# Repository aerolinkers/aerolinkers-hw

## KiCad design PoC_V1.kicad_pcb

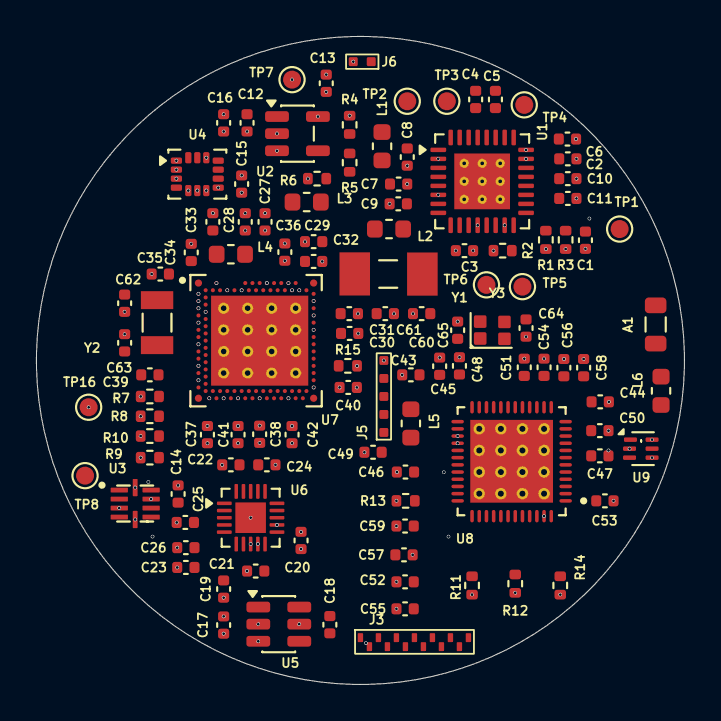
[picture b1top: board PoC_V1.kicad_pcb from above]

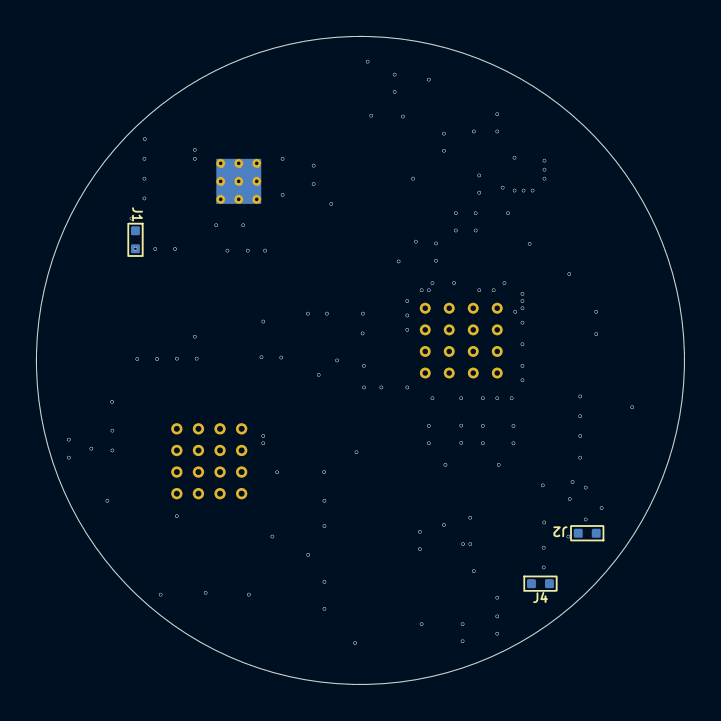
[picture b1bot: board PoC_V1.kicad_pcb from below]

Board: 4 copper layers, 36.0 x 36.0 mm, 114 parts (3 on the bottom side), 88 nets, no tracks yet.

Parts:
A1: ACA-5036-A2-CC-S - 2.4 GHz; L_0805_2012Metric
C1, C2, C4, C5, C6, C12, C14, C22, C26, C27, C28, C29, C32, C33, C45, C48, C57: 1uF; C_0402_1005Metric
C3, C15, C16, C20, C21, C23, C24, C25, C30, C34, C35, C36, C37, C38, C39, C40, C41, C42, C50, C53: 100nF; C_0402_1005Metric
C7, C8, C9, C10, C11, C13: 10uF; C_0402_1005Metric
C17, C19, C43, C47, C49, C58: 4.7uF; C_0402_1005Metric
C18, C54: 0.22uF; C_0402_1005Metric
C31: 2.2nF; C_0402_1005Metric
C44, C59: 0.47uF; C_0402_1005Metric
C46: 10nF; C_0402_1005Metric
C51, C52, C55: 2.2uF; C_0402_1005Metric
C56, C60, C61, C62, C63, C64, C65: 22nF; C_0402_1005Metric
J1, J2, J4, J6: Conn_01x02; 2P_P1mm
J3: Conn_01x13; 13P_P1mm
J5: Conn_01x05; 5P_P1mm
L1, L2: 2.2uH; L_0603_1608Metric
L3, L4: 10uH; L_0603_1608Metric
L5: 3.3uH; L_0603_1608Metric
L6: 1.5nH; L_0603_1608Metric
R1: 270K; R_0402_1005Metric
R2, R11, R12, R13, R14: 100K; R_0402_1005Metric
R3, R15: 10K; R_0402_1005Metric
R4: 200K; R_0402_1005Metric
R5: 3K; R_0402_1005Metric
R6: 66.5K; R_0402_1005Metric
R7, R8, R9, R10: 3.3K; R_0402_1005Metric
TP1, TP2, TP3, TP4, TP5, TP6, TP7, TP8, TP16: TestPoint; TestPoint_Pad_D1.0mm
U1: NPM1300-QEAA-R7; QFN-32-1EP_5x5mm_P0.5mm_EP3.1x3.1mm_ThermalVias
U2: TPS76201; SOT-23-5
U3: DRV2603; WQFN-10
U4: LSM6DSOX; LGA-14_3x2.5mm_P0.5mm_LayoutBorder3x4y
U5: REG710NA-3.3/250; SOT-23-6
U6: SGTL5000; WQFN-20-1EP_3x3mm_P0.4mm_EP1.7x1.7mm
U7: NRF5340-QKAA-AB0-R; XCVR_NRF5340-QKAA-AB0-R
U8: NRF7002-QFAA-R; IC_NRF7002-QFAA-R
U9: DPX1608LKF3R2460A; 1608 Diplexer
Y1: 32MHz; YSX530GA
Y2: 32.768 KHz; XTAL_FC-135_32.7680KA-A0
Y3: 40 MHz; 40MHZ crystal_

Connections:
DISP_3.3V: C19.1, J3.1, U5.1 (VOUT)
DIS_BL: J3.9, U7.R31 (P1.10)
DIS_CS: J3.6, U7.AK24 (P1.07)
DIS_DC: J3.7, U7.AL23 (P1.08)
DIS_MISO: J3.3, U7.AL19 (P1.04)
DIS_MOSI: J3.4, U7.AK22 (P1.05)
DIS_RST: J3.8, U7.AK26 (P1.09)
DIS_SCLK: J3.5, U7.AL21 (P1.06)
DIS_TP_INT: J3.12, U7.B14 (P1.15)
DIS_TP_RST: J3.13, U7.B20 (P1.11)
GNDREF: C1.2, C2.2, C3.2, C4.2, C5.2, C6.2, C7.2, C8.2, C9.2, C10.2, C11.2, C12.2, C13.2, C14.2, C15.2, C16.2, C17.2, C19.2, C20.2, C21.2, C22.2, C23.2, C24.2, C25.2, C26.2, C27.2, C28.2, C29.2, C30.2, C31.2, C32.2, C33.2, C34.2, C35.2, C36.2, C37.2, C38.2, C39.2, C40.2, C41.2, C42.2, C43.2, C44.2, C45.2, C46.2, C47.2, C48.2, C49.2, C50.2, C51.2, C52.2, C53.2, C54.2, C55.2, C56.2, C57.2, C58.2, C59.2, C60.2, C61.1, C62.2, C63.1, C64.2, C65.1, J1.2, J3.2, J4.2, J5.5, J6.2, R1.2, R2.2, R3.1, R6.1, R11.1, R12.1, R13.2, R14.1, U1.2 (PVSS1), U1.6 (PVSS2), U1.15 (SHPHLD), U1.23 (CC1), U1.24 (CC2), U1.33 (PAD), U2.2 (GND), U2.3 (EN), U3.3 (LRA_/ERM), U3.5 (Gnd), U3.8 (Gnd), U3.10 (Gnd), U4.1 (SDO/SA0), U4.2 (SDx), U4.3 (SCx), U4.6 (GND), U4.7 (GND), U5.2 (GND), U6.8 (LINEIN_R), U6.9 (LINEIN_L), U6.21 (Gnd_PAD), U7.35 (VSS_PAD), U7.36 (VSS_PAD), U7.37 (VSS_PAD), U7.38 (VSS_PAD), U7.39 (VSS_PAD), U7.40 (VSS_PAD), U7.41 (VSS_PAD), U7.43 (VSS_PAD), U7.44 (VSS_PAD), U7.45 (VSS_PAD), U7.46 (VSS_PAD), U7.47 (VSS_PAD), U7.48 (VSS_PAD), U7.49 (VSS_PAD), U7.50 (VSS_PAD), U7.51 (VSS_PAD), U7.104 (VSS_PAD), U7.A5 (VBUS), U7.A25 (VSS), U7.B12 (VSS), U7.B26 (VSS), U7.G1 (VSS), U7.H2 (VSS), U7.J31 (VSS), U8.27 (BUCKVSS), U8.28 (BUCKVSS), U8.47 (VSS), U8.49 (VSS), U9.2 (Gnd), U9.4 (Gnd), U9.6 (Gnd)
I2S_DIN__AUD: U6.17 (I2S_DIN), U7.AB2 (P0.06/AIN2)
I2S_DOUT__AUD: U6.16 (I2S_DOUT), U7.Y2 (P0.05/AIN1)
I2S_LRCLK__AUD: U6.14 (I2S_LRCLK), U7.AA1 (P0.03/NFC2)
I2S_SCLK__AUD: U6.15 (I2S_SCLK), U7.V2 (P0.04/AIN0)
INT1_IMU: U4.4 (INT1), U7.B16 (P1.14)
INT2_IMU: U4.9 (INT2), U7.A17 (P1.13)
MCU_2.7V: C3.1, C13.1, C15.1, C16.1, C17.1, C20.1, C27.1, C28.1, C35.1, C36.1, C37.1, C38.1, C39.1, C40.1, C41.1, C42.1, R4.2, R7.1, R8.1, R9.1, R10.1, R15.2, TP7.1, TP16.1, U1.12 (VDDIO), U2.5 (VOUT), U4.5 (VDDIO), U4.8 (VDD), U4.12 (CS), U5.3 (EN), U5.5 (VIN), U6.12 (VDDIO), U7.A19 (VDD1), U7.AC1 (VDD), U7.AG1 (VDD), U7.AJ31 (VDD), U7.AL3 (VDD), U7.AL7 (VDD), U7.AL11 (VDD), U7.AL17 (VDD), U7.AL25 (VDD), U7.B8 (VDD2), U7.B28 (VDD), U7.C1 (VDD), U7.E1 (VDDH), U7.E31 (VDD), U7.L1 (VDD3), U7.N31 (VDD), U7.U1 (VDD)
unnamed: A1.1 (FEED), L6.2
unnamed: C1.1, J1.1, U1.19 (VBAT)
unnamed: J2.1, U3.9 (OUT+)
unnamed: J2.2, U3.6 (OUT-)
unnamed: J4.1, U6.4 (HP_L)
unnamed: J5.2, R15.1, U7.AC31 (~RESET)
unnamed: J5.3, U7.W31 (SWDCLK)
unnamed: J5.4, U7.AA31 (SWDIO)
unnamed: R4.1, R5.2
unnamed: C4.1, U1.31 (LSOUT2/VOUTLDO2)
unnamed: R3.2, U1.18 (NTC)
unnamed: L1.2, U1.3 (SW1)
unnamed: L2.2, U1.5 (SW2)
unnamed: R1.1, U1.17 (VSET1)
unnamed: R2.1, U1.16 (VSET2)
unnamed: R5.1, R6.2, U2.4 (FB)
unnamed: C18.2, U5.6 (CPUMP+)
unnamed: C18.1, U5.4 (CPUMP-)
unnamed: C21.1, U6.10 (MIC)
unnamed: C23.1, U6.5 (VAG)
unnamed: L3.1, U7.A21 (DCC)
unnamed: L4.1, U7.B10 (DCCD)
unnamed: C34.1, U7.A13 (DECA)
unnamed: C33.1, L4.2, U7.A15 (DECD)
unnamed: C32.1, U7.A23 (DECN)
unnamed: C29.1, C31.1, L3.2, U7.A27 (DECR), U7.G31 (DECRF)
unnamed: C30.1, U7.L31 (ANT)
unnamed: C61.2, U7.C31 (XC1), Y1.1
unnamed: C60.1, U7.B30 (XC2), Y1.2
unnamed: C62.1, U7.N1 (P0.00/XL1), Y2.2
unnamed: C63.2, U7.R1 (P0.01/XL2), Y2.1
unnamed: C48.1, U8.19 (AFELDO)
unnamed: L5.1, U8.26 (BUCKOUT)
unnamed: C46.1, U8.29 (BUCKVMID)
unnamed: C57.1, U8.33 (DIGVDD)
unnamed: C47.1, C50.1, U8.8 (PAVDD1), U8.10 (PAVDD0), U8.12 (PALDO)
unnamed: C56.1, U8.14 (RFVDD)
unnamed: C44.1, U8.11 (SXLDO)
unnamed: C51.1, U8.16 (XOLDO)
unnamed: C65.2, U8.18 (XON), Y3.1
unnamed: C64.1, U8.17 (XOP), Y3.3
unnamed: L6.1, U9.5 (Common)
P0.12: R13.1, U7.AK6 (P0.12/TRACECLK), U8.30 (BUCKEN)
P0.23: U7.AK20 (P0.23), U8.46 (HOST_IRQ)
P0.24: U7.AL27 (P0.24), U8.43 (COEX_GRANT)
P0.28: R12.2, U7.AE31 (P0.28/AIN7), U8.42 (COEX_REQ)
P0.29: R14.2, U7.U31 (P0.29), U8.45 (SW_CTRL1)
P0.30: R11.2, U7.B24 (P0.30), U8.41 (COEX_STATUS0)
PWM_HD: TP8.1, U3.2 (PWM), U7.M2 (P1.00)
PWRIOVDD: C52.1, C53.1, C55.1, U8.1 (OTPVDD), U8.34 (PWRIOVDD)
QSPI_CLK: U7.AK12 (P0.17/QPSI_CLK), U8.35 (QSPI_CLK/SPI_CLK)
QSPI_DATA0: U7.AL5 (P0.13/QPSI_[0]), U8.37 (QSPI_DATA0/SPI_MOSI)
QSPI_DATA1: U7.AK8 (P0.14/QPSI_[1]), U8.38 (QSPI_DATA1/SPI_MISO)
QSPI_DATA2: U7.AK10 (P0.15/QPSI_[2]), U8.39 (QSPI_DATA2)
QSPI_DATA3: U7.AL9 (P0.16/QPSI_[3]), U8.40 (QSPI_DATA3)
QSPI_SS: U7.AK14 (P0.18/QPSI_CS), U8.36 (QSPI_SS/SPI_SS)
SCL_AUD: R9.2, U6.19 (CTRL_CLK), U7.AH2 (P0.08/TRACEDATA[3])
SCL_MAIN: J3.11, R7.2, TP5.1, U1.14 (SCL), U4.13 (SCL), U7.AE1 (P1.02/I2C)
SDA_AUD: R10.2, U6.18 (CTRL_DATA), U7.AD2 (P0.07/AIN3)
SDA_MAIN: J3.10, R8.2, TP6.1, U1.13 (SDA), U4.14 (SDA), U7.AF2 (P1.03.I2C)
SYS_MCLK_AUD: U6.13 (SYS_MCLK), U7.W1 (P0.02/NFC1)
TXRF0: U8.9 (TXRF0), U9.1 (2.4G)
TXRF1: U8.7 (TXRF1), U9.3 (5G)
VAUD-2 _ 1.8V: C5.1, C22.1, C24.1, TP4.1, U1.29 (LSOUT1/VOUTLDO1), U6.20 (VDDD)
VBUSIN: C2.1, J6.1, U1.21 (VBUS)
VBUSOUT: C6.1, U1.22 (VBUSOUT)
VDD_BUCK: C49.1, C54.1, C59.1, L5.2, U8.15 (RFBUCKVDD), U8.32 (PWRBUCKVDD)
VPER-1 _ 2.7V: C8.1, C14.1, C25.1, C26.1, L1.1, TP2.1, U1.1 (VOUT1), U3.1 (EN), U3.7 (VDD), U6.3 (VDDA)
VPER-2 _ 2.7V: C9.1, C43.1, C45.1, C58.1, L2.1, TP3.1, U1.32 (VOUT2), U8.13 (VBAT), U8.20 (AFEVBAT), U8.25 (BUCKVBAT), U8.31 (BUCKVBATS), U8.48 (IOVDD)
VSYS: C7.1, C10.1, C11.1, C12.1, J5.1, TP1.1, U1.4 (PVDD), U1.20 (VSYS), U2.1 (VIN)

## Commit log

2026-04-11 schmatics
2026-04-12 VSET1 & Ref1 updated
2026-04-12 Ref link added & Removed charge pumps
2026-04-12 added gitignore file
2026-04-12 Updated Schematic.pdf
2026-04-12 Added README.md
2026-04-13 Chnaged Battery symbol
2026-04-13 LDO feedback resistor updated
2026-04-13 Motor, Speaker symbols updated and ref. updated
2026-04-13 Updated capcitors value of XL1 and XL2
2026-04-13 updated version
